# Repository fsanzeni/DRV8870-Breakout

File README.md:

# DRV8870 Breakout Board

A simple breakout board for the [Texas Instruments DRV8870](https://www.ti.com/product/DRV8870) brushed DC motor driver (up to 3.6A peak current).

## Features

- **Motor Driver:** TI DRV8870DDA H-Bridge Motor Driver
- **Wide Operating Voltage:** VDC input ranges from 6.5V to 45V
- **Adjustable VREF:** Includes a trim potentiometer to easily set the VREF between ~1V and ~5V
- **Flexible Control:** The IN1 and IN2 pins can be driven externally via an MCU (via PWM) or set manually using jumpers.

## Hardware Overview

### Connectors
- **J1 (Voltage Input):** VDC and GND. Connect your main motor power supply here (6.5V-45V).
- **J3 (Motor Output):** OUT1 and OUT2. Connect directly to your brushed DC motor.
- **J2 & J4 (IO Connectors):** IN1 and IN2 logic inputs for controlling motor direction and state.

### Test Points
The board includes numerous test points (TP1-TP12) across VDC, +5V, GND, IN1, IN2, VREF, OUT1, and OUT2 for easy probing and debugging.

### Control Logic

| IN1 | IN2 | OUT1 | OUT2 | Description |
| :---: | :---: | :---: | :---: | :--- |
| 0 | 0 | High-Z | High-Z | Coast; H-Bridge disabled to High-Z |
| 0 | 1 | L | H | Reverse |
| 1 | 0 | H | L | Forward |
| 1 | 1 | L | L | Brake; low-side decay |

*Note: For more information on VREF and current regulation, refer to [page 8 of the DRV8870 datasheet](https://www.ti.com/lit/ds/symlink/drv8870.pdf?ts=1774725556213).*

## License

This project is licensed under the MIT License.

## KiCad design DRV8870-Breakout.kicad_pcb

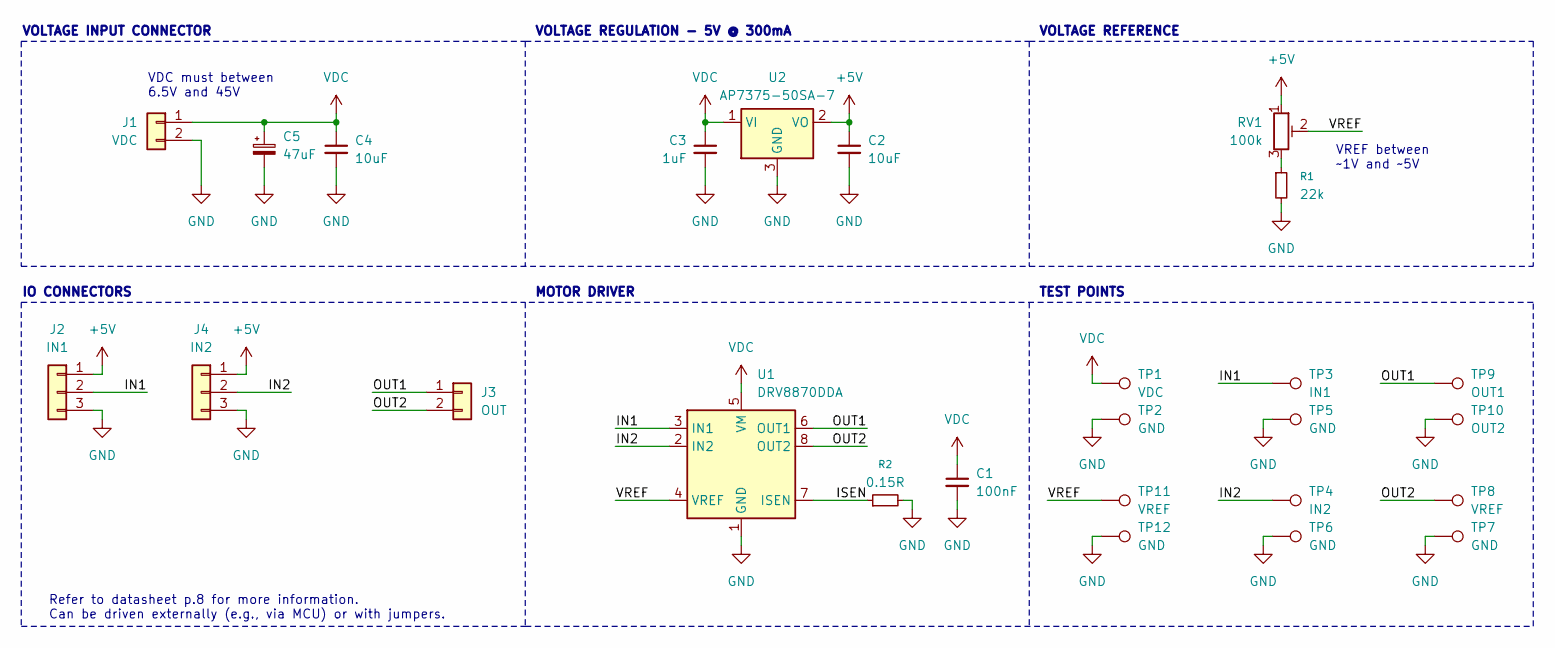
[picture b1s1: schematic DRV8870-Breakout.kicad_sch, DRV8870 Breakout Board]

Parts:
C1: 100nF; C_0603_1608Metric
C2, C4: 10uF; C_0603_1608Metric
C3: 1uF; C_0603_1608Metric
C5: 47uF; CP_Elec_6.3x7.7
J1: VDC; TerminalBlock_CUI_TB007-508-02_1x02_P5.08mm_Horizontal
J2: IN1; PinHeader_1x03_P2.54mm_Vertical
J3: OUT; TerminalBlock_CUI_TB007-508-02_1x02_P5.08mm_Horizontal
J4: IN2; PinHeader_1x03_P2.54mm_Vertical
R1: 22k; R_0603_1608Metric
R2: 0.15R; R_1206_3216Metric
RV1: 100k; Potentiometer_Bourns_3296W_Vertical
TP1: VDC; TestPoint_Pad_D1.5mm
TP2, TP5, TP6, TP7, TP12: GND; TestPoint_Pad_D1.5mm
TP3: IN1; TestPoint_Pad_D1.5mm
TP4: IN2; TestPoint_Pad_D1.5mm
TP8, TP11: VREF; TestPoint_Pad_D1.5mm
TP9: OUT1; TestPoint_Pad_D1.5mm
TP10: OUT2; TestPoint_Pad_D1.5mm
U1: DRV8870DDA; Texas_HTSOP-8-1EP_3.9x4.9mm_P1.27mm_EP2.95x4.9mm_Mask2.4x3.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
U2: AP7375-50SA-7; SOT-23-3

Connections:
+5V: C2.1, J2.1, J4.1, RV1.1, U2.2 (VO)
/IN1: J2.2, TP3.1, U1.3 (IN1)
/IN2: J4.2, TP4.1, U1.2 (IN2)
/ISEN: R2.1, U1.7 (ISEN)
/OUT1: J3.1, TP9.1, U1.6 (OUT1)
/OUT2: J3.2, TP8.1, U1.8 (OUT2)
/VREF: RV1.2, TP11.1, U1.4 (VREF)
GND: C1.2, C2.2, C3.2, C4.2, C5.2, J1.2, J2.3, J4.3, R1.2, R2.2, TP2.1, TP5.1, TP6.1, TP7.1, TP10.1, TP12.1, U1.1 (GND), U1.9 (GND), U2.3 (GND)
unnamed: R1.1, RV1.3
VDC: C1.1, C3.1, C4.1, C5.1, J1.1, TP1.1, U1.5 (VM), U2.1 (VI)

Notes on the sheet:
IO CONNECTORS
Refer to datasheet p.8 for more information. Can be driven externally (e.g., via MCU) or with jumpers.
VOLTAGE REGULATION - 5V @ 300mA
VOLTAGE INPUT CONNECTOR
TEST POINTS
VDC must between 6.5V and 45V
VOLTAGE REFERENCE
MOTOR DRIVER
VREF between ~1V and ~5V

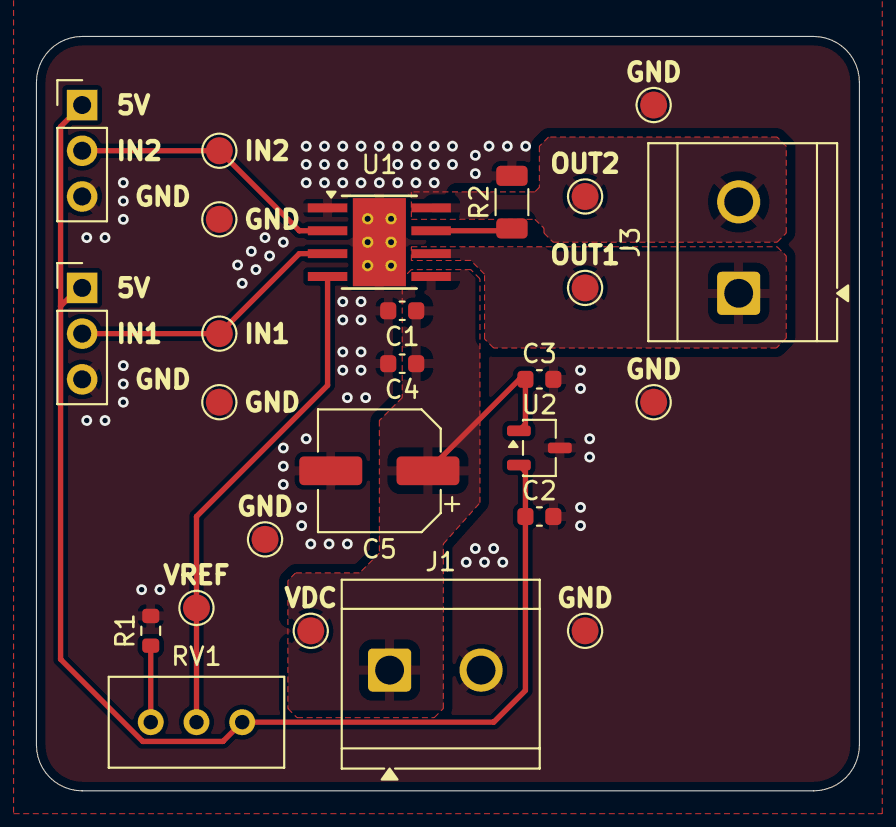
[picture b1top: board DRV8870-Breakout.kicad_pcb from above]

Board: 2 copper layers, 45.7 x 41.9 mm, 26 parts (0 on the bottom side), 10 nets.

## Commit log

2026-03-28 finish design.
